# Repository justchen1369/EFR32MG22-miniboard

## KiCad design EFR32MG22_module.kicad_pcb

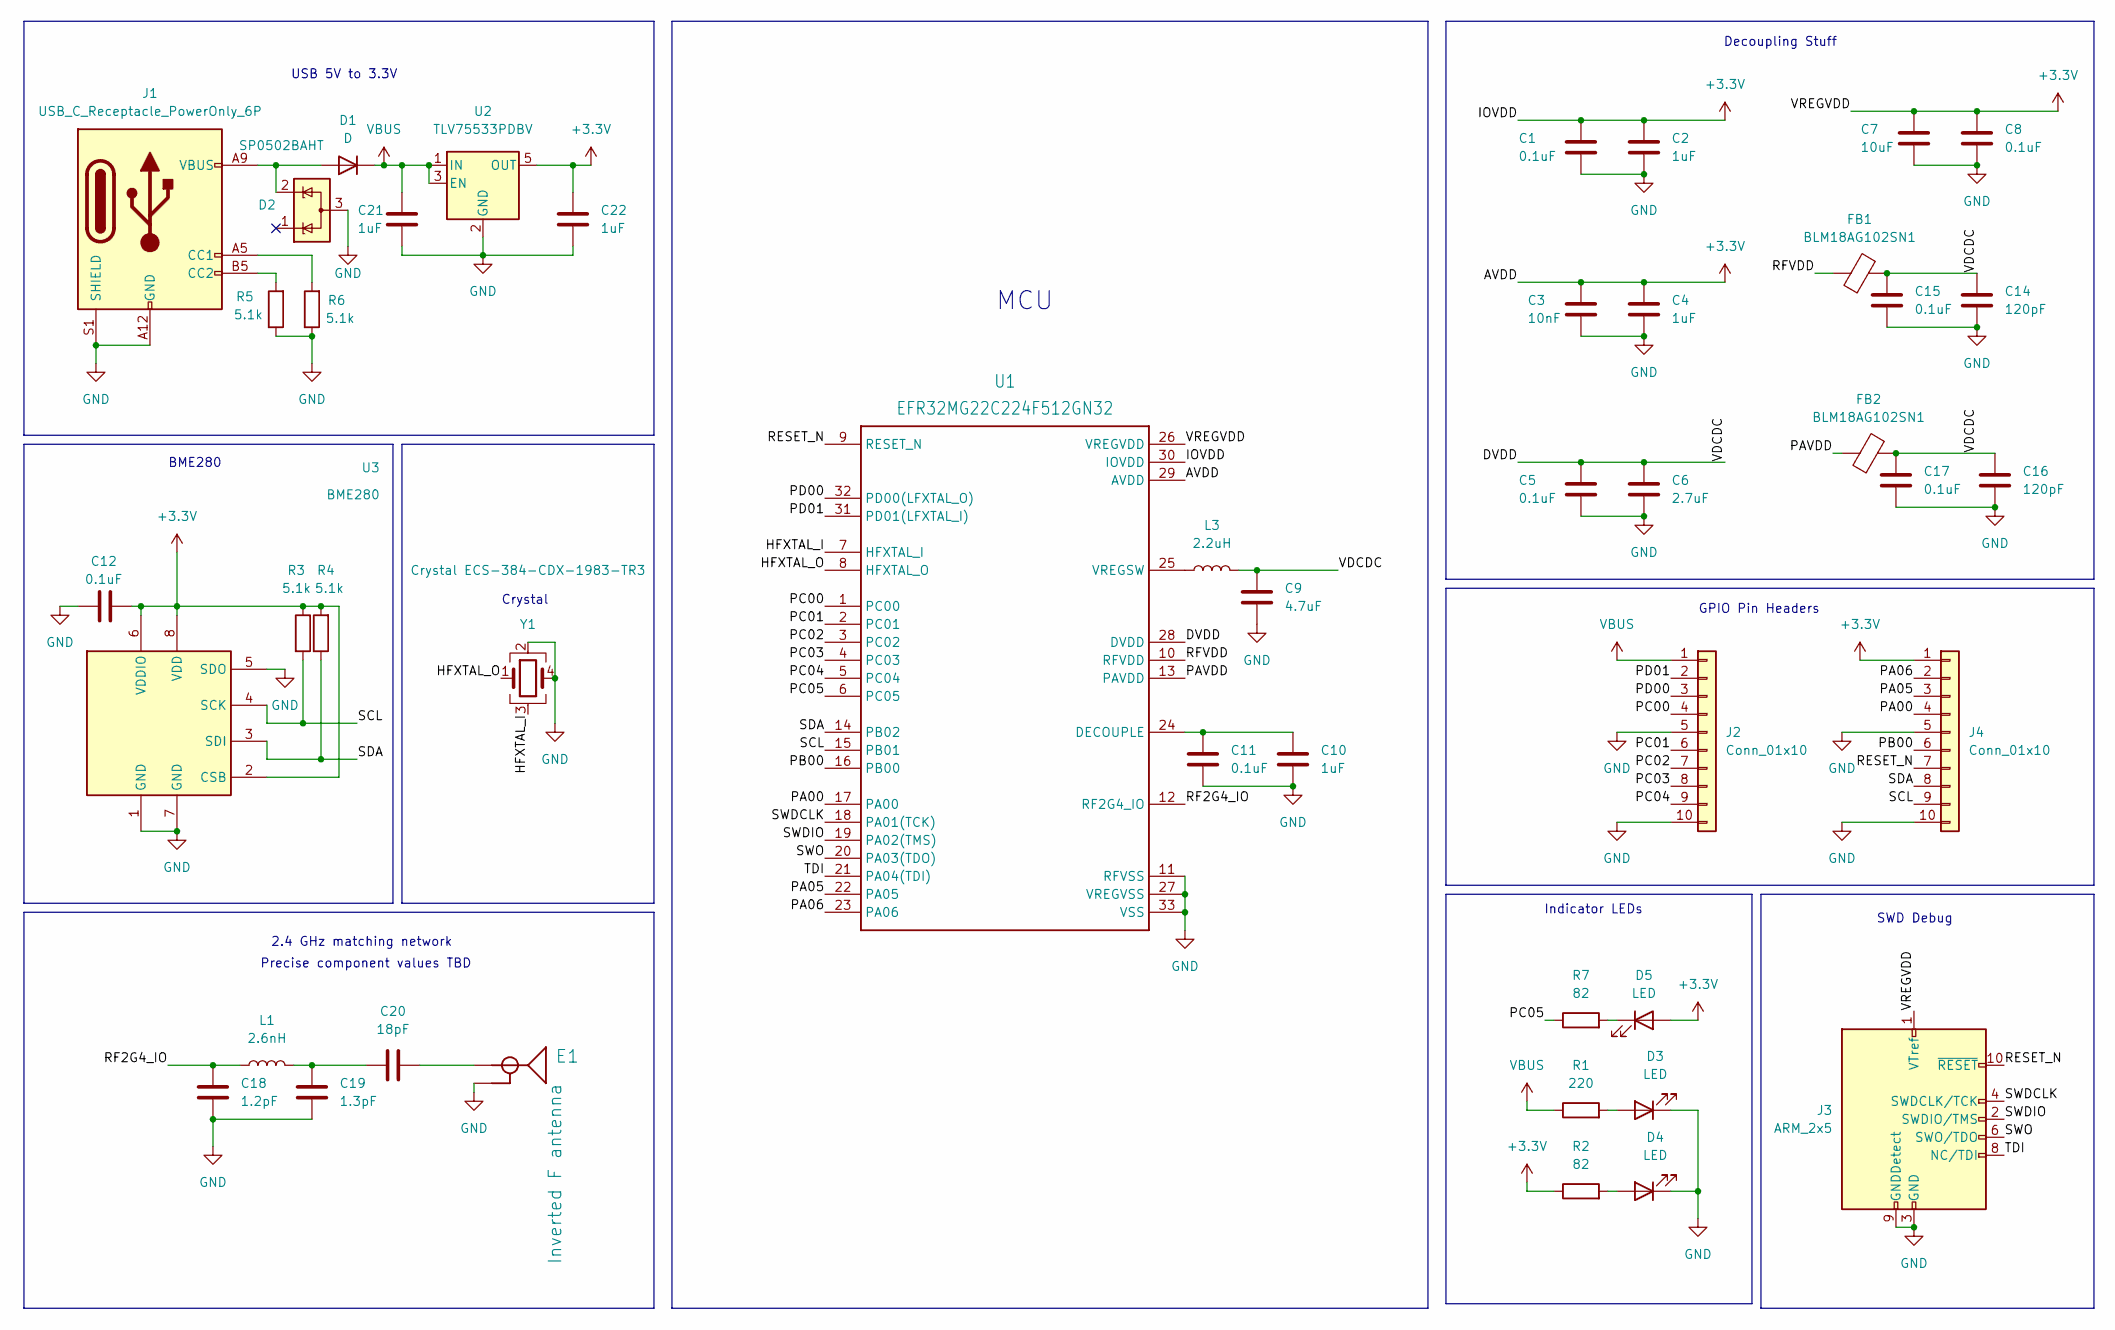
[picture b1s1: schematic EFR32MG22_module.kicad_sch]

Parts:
C1, C5, C8, C11, C12, C15, C17: 0.1uF; C_0402_1005Metric_Pad0.74x0.62mm_HandSolder
C2, C4, C10, C21, C22: 1uF; C_0402_1005Metric_Pad0.74x0.62mm_HandSolder
C3: 10nF; C_0402_1005Metric_Pad0.74x0.62mm_HandSolder
C6: 2.7uF; C_0603_1608Metric_Pad1.08x0.95mm_HandSolder
C7: 10uF; C_0603_1608Metric_Pad1.08x0.95mm_HandSolder
C9: 4.7uF; C_0603_1608Metric_Pad1.08x0.95mm_HandSolder
C14, C16: 120pF; C_0402_1005Metric_Pad0.74x0.62mm_HandSolder
C18: 1.2pF; C_0402_1005Metric_Pad0.74x0.62mm_HandSolder
C19: 1.3pF; C_0402_1005Metric_Pad0.74x0.62mm_HandSolder
C20: 18pF; C_0402_1005Metric_Pad0.74x0.62mm_HandSolder
D1: D; D_SOD-123
D2: SP0502BAHT; SOT-23
D3, D4, D5: LED; D_0603_1608Metric_Pad1.05x0.95mm_HandSolder
E1: Inverted F antenna; TRACE_ANTENNA_2.4GHZ_15.2MM
FB1, FB2: BLM18AG102SN1; L_0603_1608Metric_Pad1.05x0.95mm_HandSolder
J1: USB_C_Receptacle_PowerOnly_6P; USB_C_Receptacle_GCT_USB4125-xx-x-0190_6P_TopMnt_Horizontal
J2, J4: Conn_01x10; PinHeader_1x10_P2.54mm_Vertical
J3: ARM_2x5; CNC_Tech_2x5_ARM_DEBUG
L1: 2.6nH; L_0402_1005Metric_Pad0.77x0.64mm_HandSolder
L3: 2.2uH; L_0805_2012Metric_Pad1.15x1.40mm_HandSolder
R1: 220; R_0402_1005Metric_Pad0.72x0.64mm_HandSolder
R2, R7: 82; R_0402_1005Metric_Pad0.72x0.64mm_HandSolder
R3, R4, R5, R6: 5.1k; R_0402_1005Metric_Pad0.72x0.64mm_HandSolder
U1: EFR32MG22C224F512GN32; QFN-32-1EP_4x4mm_P0.4mm_EP2.9x2.9mm_ThermalVias
U2: TLV75533PDBV; SOT-23-5
U3: BME280; Bosch_LGA-8_2.5x2.5mm_P0.65mm_ClockwisePinNumbering
Y1: Crystal ECS-384-CDX-1983-TR3; Crystal_SMD_2016-4Pin_2.0x1.6mm

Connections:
+3.3V: C1.1, C2.1, C3.1, C4.1, C7.1, C8.1, C12.2, C22.2, D5.2 (A), J3.1 (VTref), J4.1, R2.1, R3.1, R4.2, U1.26 (VREGVDD), U1.29 (AVDD), U1.30 (IOVDD), U2.5 (OUT), U3.2 (CSB), U3.6 (VDDIO), U3.8 (VDD)
/DVDD: C5.1, C6.1, C9.1, C14.1, C15.1, C16.1, C17.1, FB1.2, FB2.2, L3.2, U1.28 (DVDD)
/HFXTAL_I: U1.7 (HFXTAL_I), Y1.3
/HFXTAL_O: U1.8 (HFXTAL_O), Y1.1
/PA00: J4.4, U1.17 (PA00)
/PA05: J4.3, U1.22 (PA05)
/PA06: J4.2, U1.23 (PA06)
/PAVDD: FB2.1, U1.13 (PAVDD)
/PB00: J4.6, U1.16 (PB00)
/PC00: J2.4, U1.1 (PC00)
/PC01: J2.6, U1.2 (PC01)
/PC02: J2.7, U1.3 (PC02)
/PC03: J2.8, U1.4 (PC03)
/PC04: J2.9, U1.5 (PC04)
/PC05: R7.1, U1.6 (PC05)
/PD00: J2.3, U1.32 (PD00(LFXTAL_O))
/PD01: J2.2, U1.31 (PD01(LFXTAL_I))
/RESET_N: J3.10 (~RESET), J4.7, U1.9 (RESET_N)
/RF2G4_IO: C18.1, L1.1, U1.12 (RF2G4_IO)
/RFVDD: FB1.1, U1.10 (RFVDD)
/SCL: J4.9, R3.2, U1.15 (PB01), U3.4 (SCK)
/SDA: J4.8, R4.1, U1.14 (PB02), U3.3 (SDI)
/SWDCLK: J3.4 (SWDCLK/TCK), U1.18 (PA01(TCK))
/SWDIO: J3.2 (SWDIO/TMS), U1.19 (PA02(TMS))
/SWO: J3.6 (SWO/TDO), U1.20 (PA03(TDO))
/TDI: J3.8 (NC/TDI), U1.21 (PA04(TDI))
GND: C1.2, C2.2, C3.2, C4.2, C5.2, C6.2, C7.2, C8.2, C9.2, C10.2, C11.2, C12.1, C14.2, C15.2, C16.2, C17.2, C18.2, C19.2, C21.1, C22.1, D2.3 (A), D3.1 (K), D4.1 (K), E1.GND, J1.A12 (GND), J1.B12 (GND), J1.S1 (SHIELD), J2.5, J2.10, J3.3 (GND), J3.5 (GND), J3.9 (GNDDetect), J4.5, J4.10, R5.1, R6.1, U1.11 (RFVSS), U1.27 (VREGVSS), U1.33 (VSS), U2.2 (GND), U3.1 (GND), U3.5 (SDO), U3.7 (GND), Y1.2, Y1.4
unnamed: C19.1, C20.2, L1.2
unnamed: D1.2 (A), D2.2 (K), J1.A9 (VBUS), J1.B9 (VBUS)
unnamed: D3.2 (A), R1.2
unnamed: D4.2 (A), R2.2
unnamed: D5.1 (K), R7.2
unnamed: C20.1, E1.ANT (SIGNAL)
unnamed: J1.A5 (CC1), R6.2
unnamed: J1.B5 (CC2), R5.2
unnamed: C10.1, C11.1, U1.24 (DECOUPLE)
unnamed: L3.1, U1.25 (VREGSW)
VBUS: C21.2, D1.1 (K), J2.1, R1.1, U2.1 (IN), U2.3 (EN)

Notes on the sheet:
MCU
Indicator LEDs
GPIO Pin Headers
Precise component values TBD
2.4 GHz matching network
SWD Debug
Crystal
BME280
Decoupling Stuff
USB 5V to 3.3V

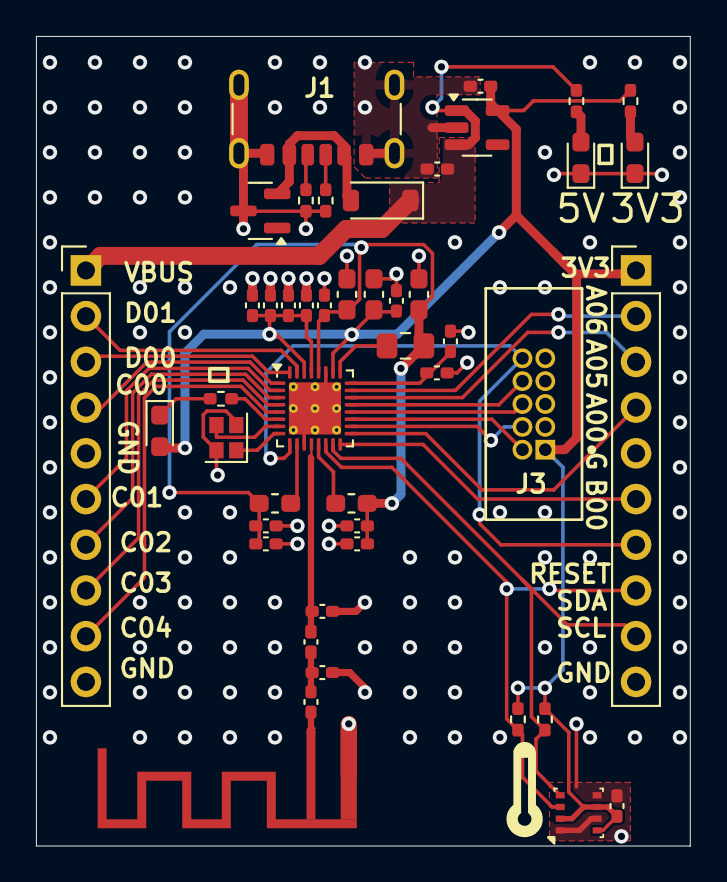
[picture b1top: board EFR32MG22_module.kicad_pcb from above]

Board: 4 copper layers, 36.3 x 45.0 mm, 46 parts (0 on the bottom side), 38 nets.

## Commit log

2022-11-19 better routing of ARM debug connector
2022-12-01 final commit? (?)
2025-01-25 first pass at layout and routing for second revision
2025-01-26 add impedance-controlled trace for antenna
2025-01-28 minor tweaks for component selection
2025-01-29 fix DRC
2025-01-29 silkscreen
